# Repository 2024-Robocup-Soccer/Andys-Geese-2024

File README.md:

<h1 align="center" id="title">Robocup Soccer</h1>

<p id="description">A Lightweight Soccer Robot for Robocup Junior. Created by Matteo Cericola, John Qing, Sean Yien and Yuan Yoshimi. </p>

Documentation: https://andys-geese-2024.readthedocs.io/en/latest/

RoboCup is an international robotics tournament held around the world every year. More information can be found here: https://www.robocup.org/. The tournament we participated in this year was RoboCup Junior Lightweight.

<h2>Competition and Awards</h2>

2024 RCJ National Soccer Champion (Toronto)

2024 RCJ Regional Soccer Champion (Montreal)

2024 RCJ Regional Soccer Super Team Champion (Montreal)

<h2>3D Model Link</h2>

[https://a360.co/3x0yv2s](https://a360.co/3x0yv2s)

<h2>Project Pictures:</h2>

<h2>💻 Built with</h2>

Technologies used in the project:

*   Fusion 360
*   VS Code (PlatformIO)
*   Prusa MK4 3D Printer
*   Teensy 4.1
*   OpenMv Camera
*   Adafruit BNO085 Compass
*   TSSP4038
*   GTF 50mm Omniwheels
*   GA25YN370 12V 1000RPM Motors
*   Pololu G2 High-Power Motor Driver 18v25
*   Photodiodes

CC BY-SA 4.0

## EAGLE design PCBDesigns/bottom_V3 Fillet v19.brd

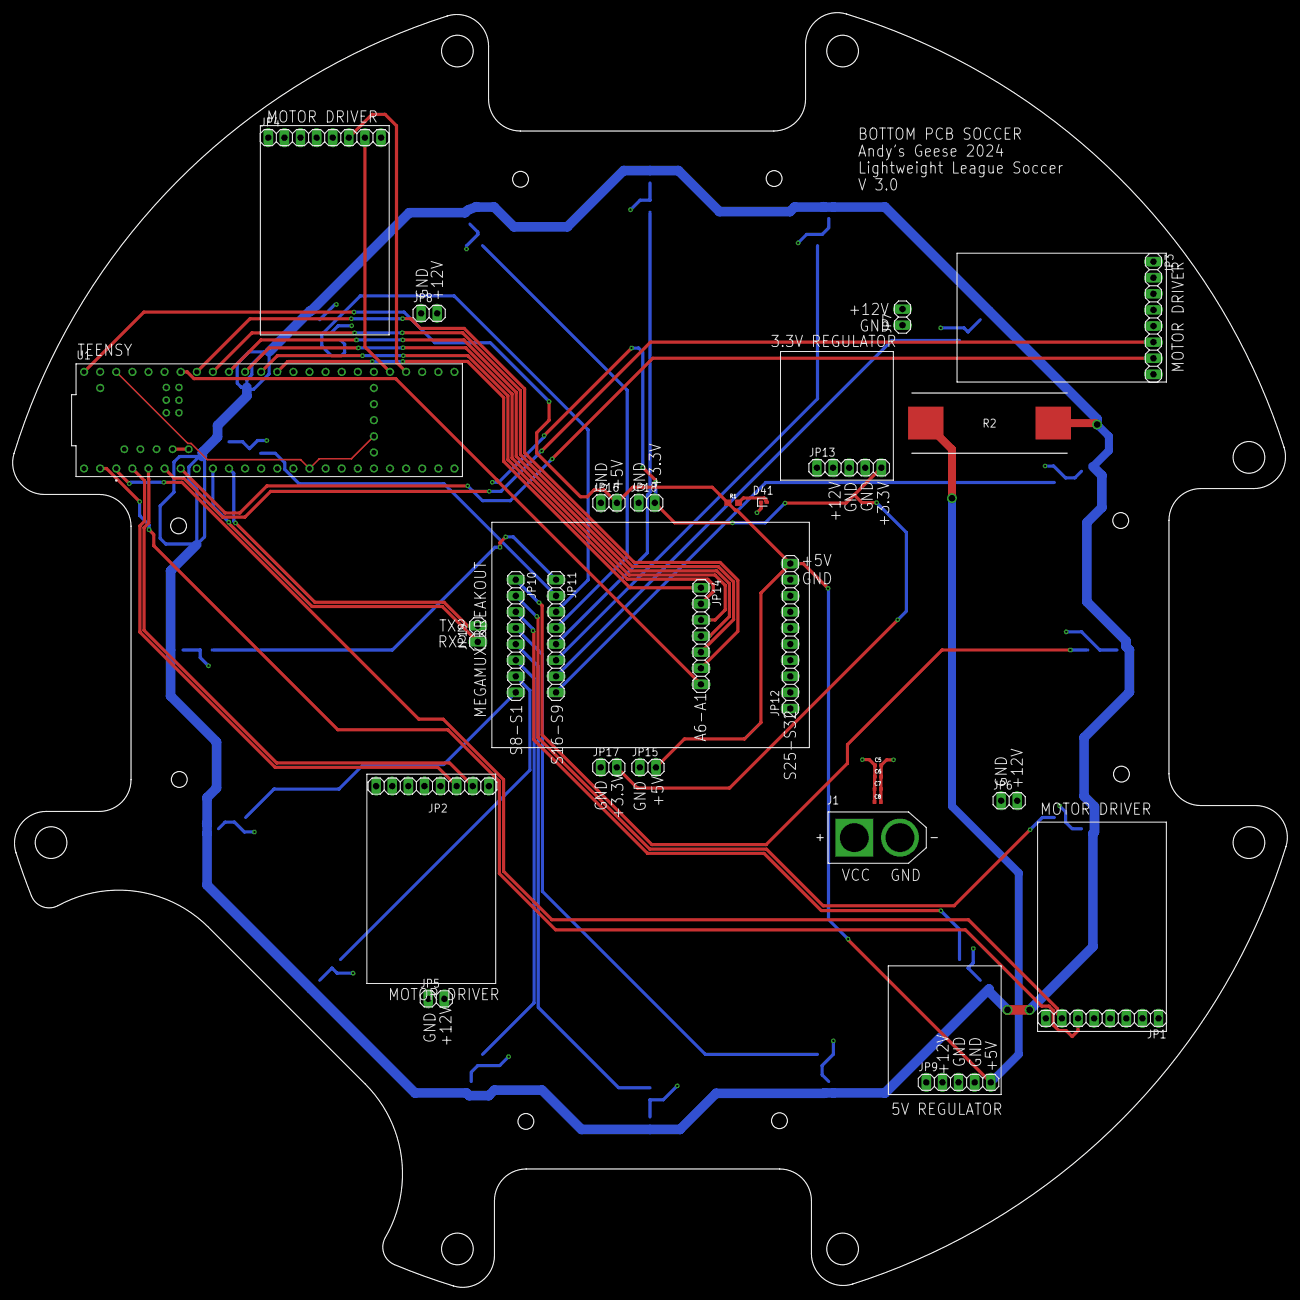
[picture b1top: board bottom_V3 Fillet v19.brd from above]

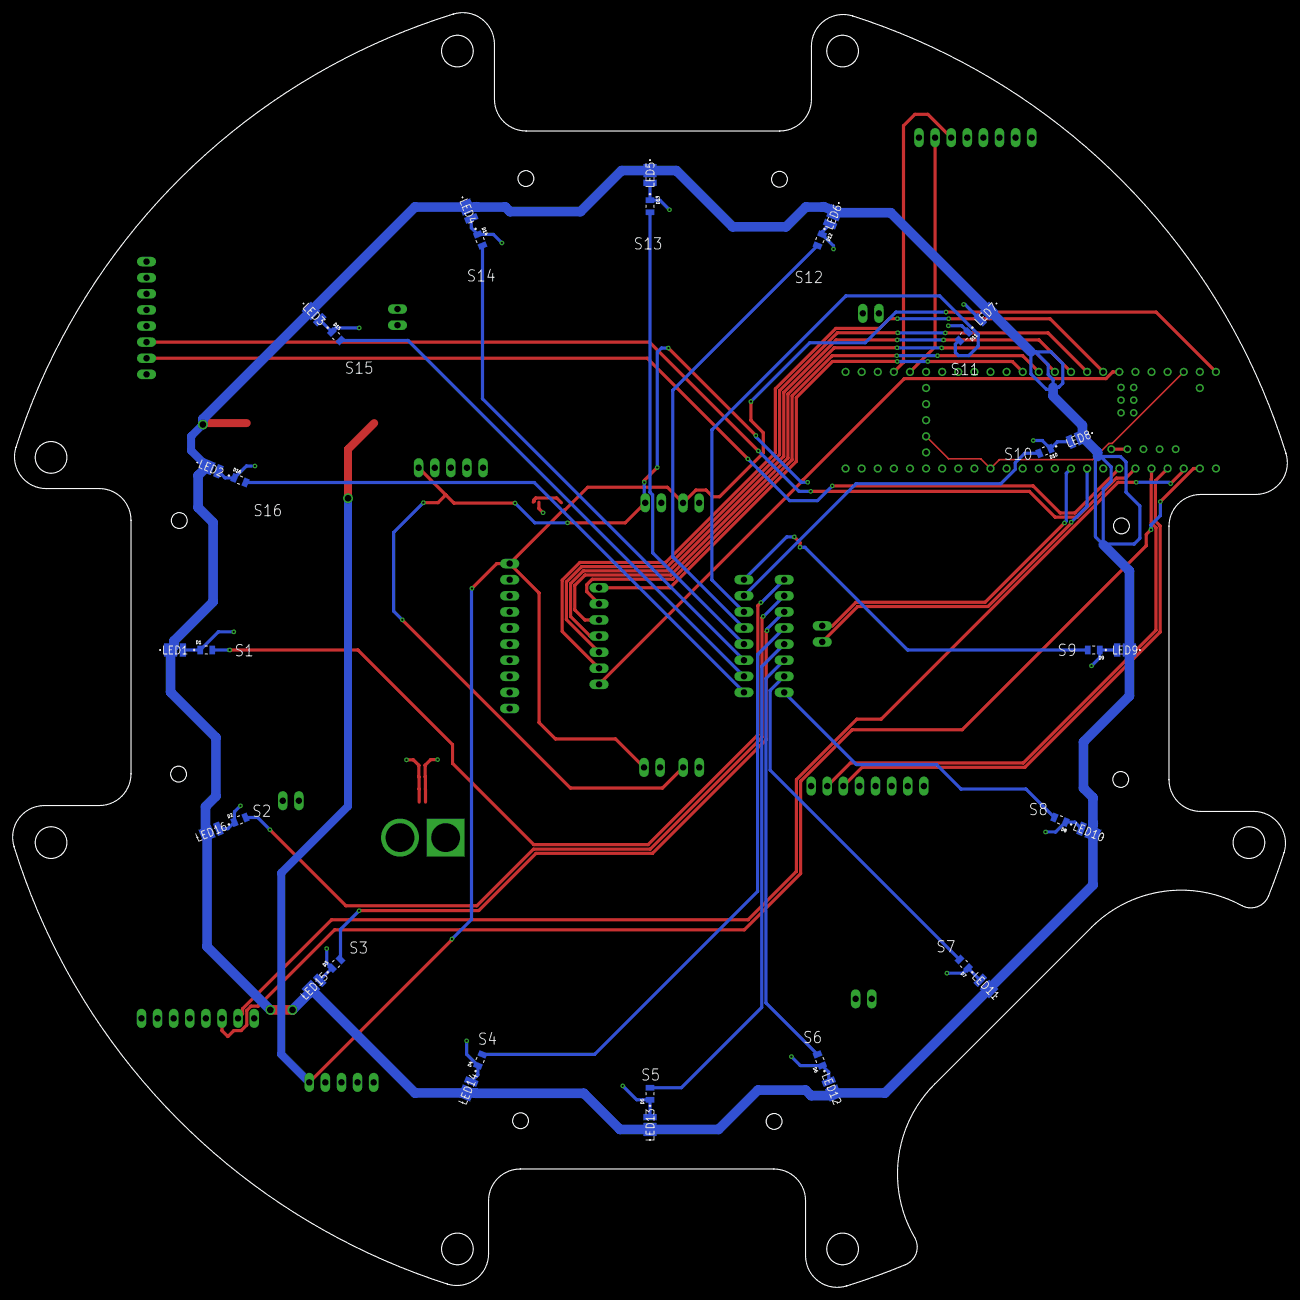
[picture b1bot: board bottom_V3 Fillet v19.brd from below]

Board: 4 copper layers, 201.1 x 201.1 mm, 60 parts (32 on the bottom side), 41 nets.

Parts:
C5, C6, C7, C8: 0.1uF; 0402-TIGHT
D1, D2, D3, D4, D5, D6, D7, D8, D9, D10, D11, D12, D13, D14, D15, D16: 019-141-411-R; DIOC2012X80N
D41: LED_GREEN; LEDC1005X25N_FLAT-G
J1: XT60-M; AMASS_XT60-M
JP1, JP2, JP3, JP4, JP10, JP11: PINHD-1X8; 1X08
JP5, JP6, JP7, JP8, JP15, JP16, JP17, JP18, JP19: PINHD-1X2; 1X02
JP9, JP13: PINHD-1X5; 1X05
JP12: PINHD-1X10; 1X10
JP14: PINHD-1X7; 1X07
LED1, LED2, LED3, LED4, LED5, LED6, LED7, LED8, LED9, LED10, LED11, LED12, LED13, LED14, LED15, LED16: 150283HS73103
R1: 1k; 0603
R2: SMW71R5JT; RESM24595X990N
U1: DEV-16771; MODULE_DEV-16771

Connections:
0: JP1.6, U1.0
1: JP1.7, U1.1
2: JP2.6, U1.2
3: JP2.7, U1.3
3.3V: U1.3.3V_1, U1.3.3V_2, U1.3.3V_3
4: JP3.6, U1.4
5: JP3.7, U1.5
36: JP4.6, U1.36
37: JP4.7, U1.37
+3.3V: JP13.5, JP17.2, JP18.2
+5V: JP9.5, JP12.10, JP15.2, JP16.2, R1.1, R2.1, U1.VIN
A0: JP14.1, U1.14
A1: JP14.2, U1.15
A2: JP14.3, U1.16
A3: JP14.4, U1.17
A4: JP14.5, U1.18
A5: JP14.6, U1.19
A6: JP14.7, U1.20
GND: C5.2, C6.2, C7.2, C8.2, D1.K, D2.K, D3.K, D4.K, D5.K, D6.K, D7.K, D8.K, D9.K, D10.K, D11.K, D12.K, D13.K, D14.K, D15.K, D16.K, D41.C, J1.N, JP1.8, JP2.8, JP3.8, JP4.8, JP5.1, JP6.1, JP7.1, JP8.1, JP9.3, JP9.4, JP12.9, JP13.3, JP13.4, JP15.1, JP16.1, JP17.1, JP18.1, LED1.2, LED2.2, LED3.2, LED4.2, LED5.2, LED6.2, LED7.2, LED8.2, LED9.2, LED10.2, LED11.2, LED12.2, LED13.2, LED14.2, LED15.2, LED16.2, U1.GND1, U1.GND2, U1.GND3, U1.GND4, U1.GND5
unnamed: LED1.1, LED2.1, LED3.1, LED4.1, LED5.1, LED6.1, LED7.1, LED8.1, LED9.1, LED10.1, LED11.1, LED12.1, LED13.1, LED14.1, LED15.1, LED16.1, R2.2
unnamed: D41.A, R1.2
RX2: JP19.1, U1.7
S1: D1.A, JP10.1
S2: D2.A, JP10.2
S3: D3.A, JP10.3
S4: D4.A, JP10.4
S5: D5.A, JP10.5
S6: D6.A, JP10.6
S7: D7.A, JP10.7
S8: D8.A, JP10.8
S9: D9.A, JP11.1
S10: D10.A, JP11.2
S11: D11.A, JP11.3
S12: D12.A, JP11.4
S13: D13.A, JP11.5
S14: D14.A, JP11.6
S15: D15.A, JP11.7
S16: D16.A, JP11.8
TX2: JP19.2, U1.8
USB_GND: U1.USB_GND1, U1.USB_GND2
VCC: C5.1, C6.1, C7.1, C8.1, J1.P, JP5.2, JP6.2, JP7.2, JP8.2, JP9.2, JP13.2

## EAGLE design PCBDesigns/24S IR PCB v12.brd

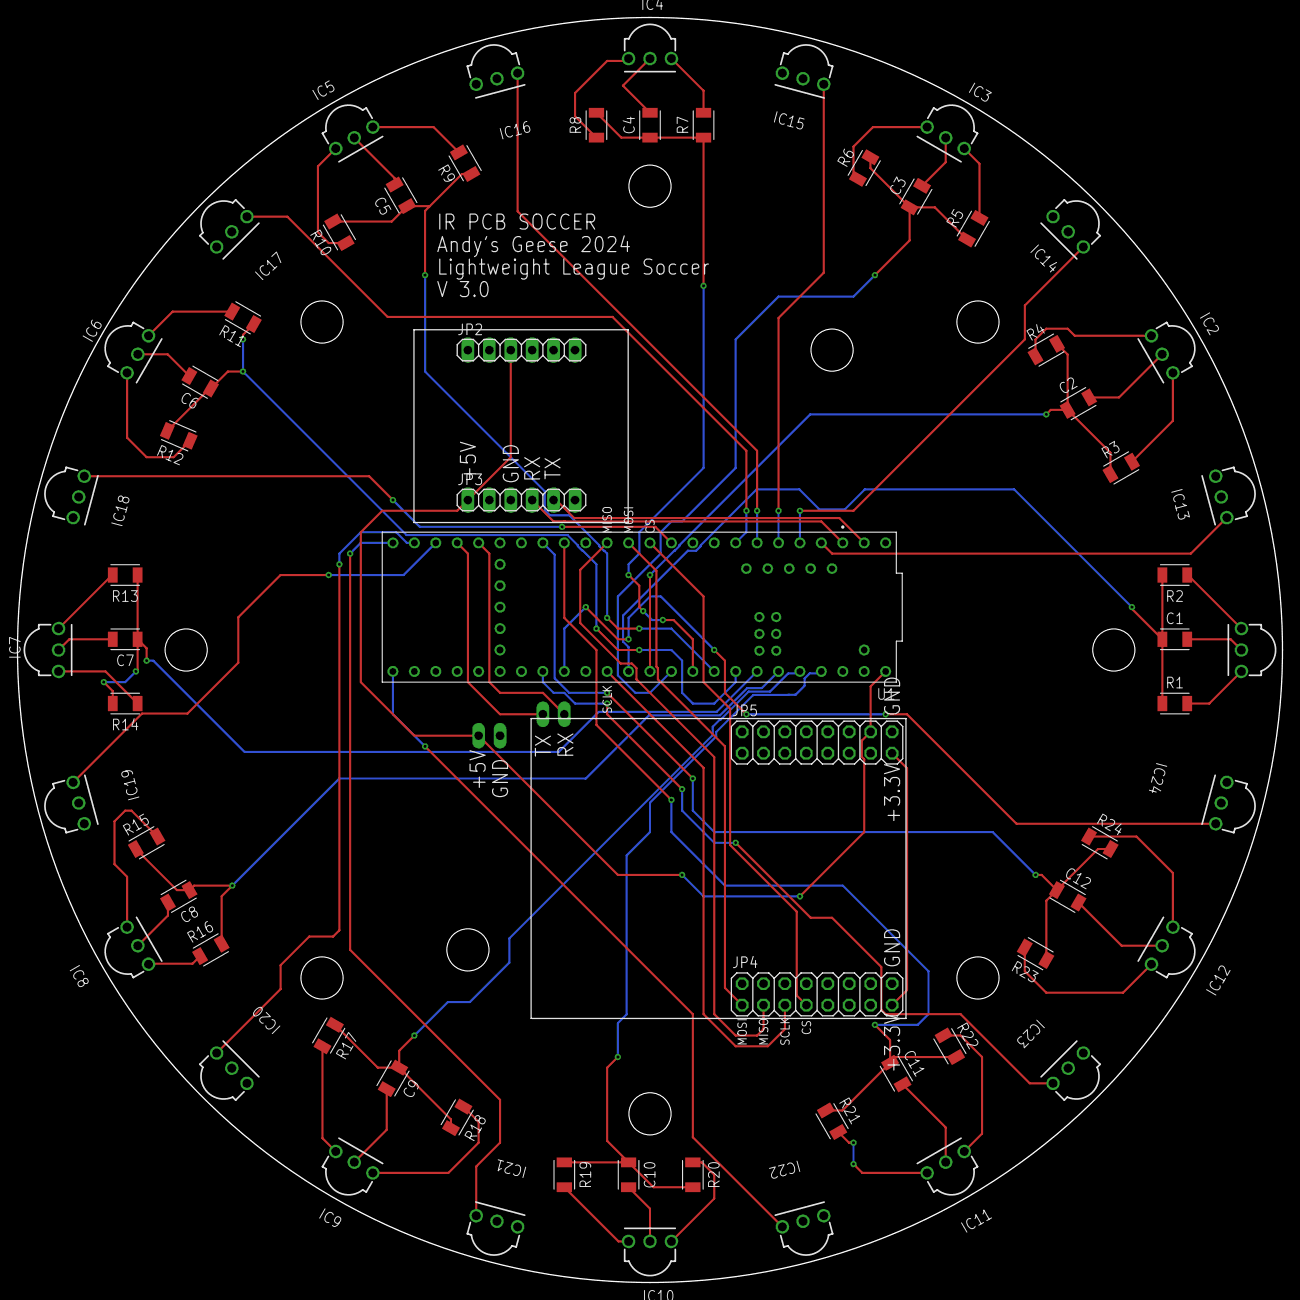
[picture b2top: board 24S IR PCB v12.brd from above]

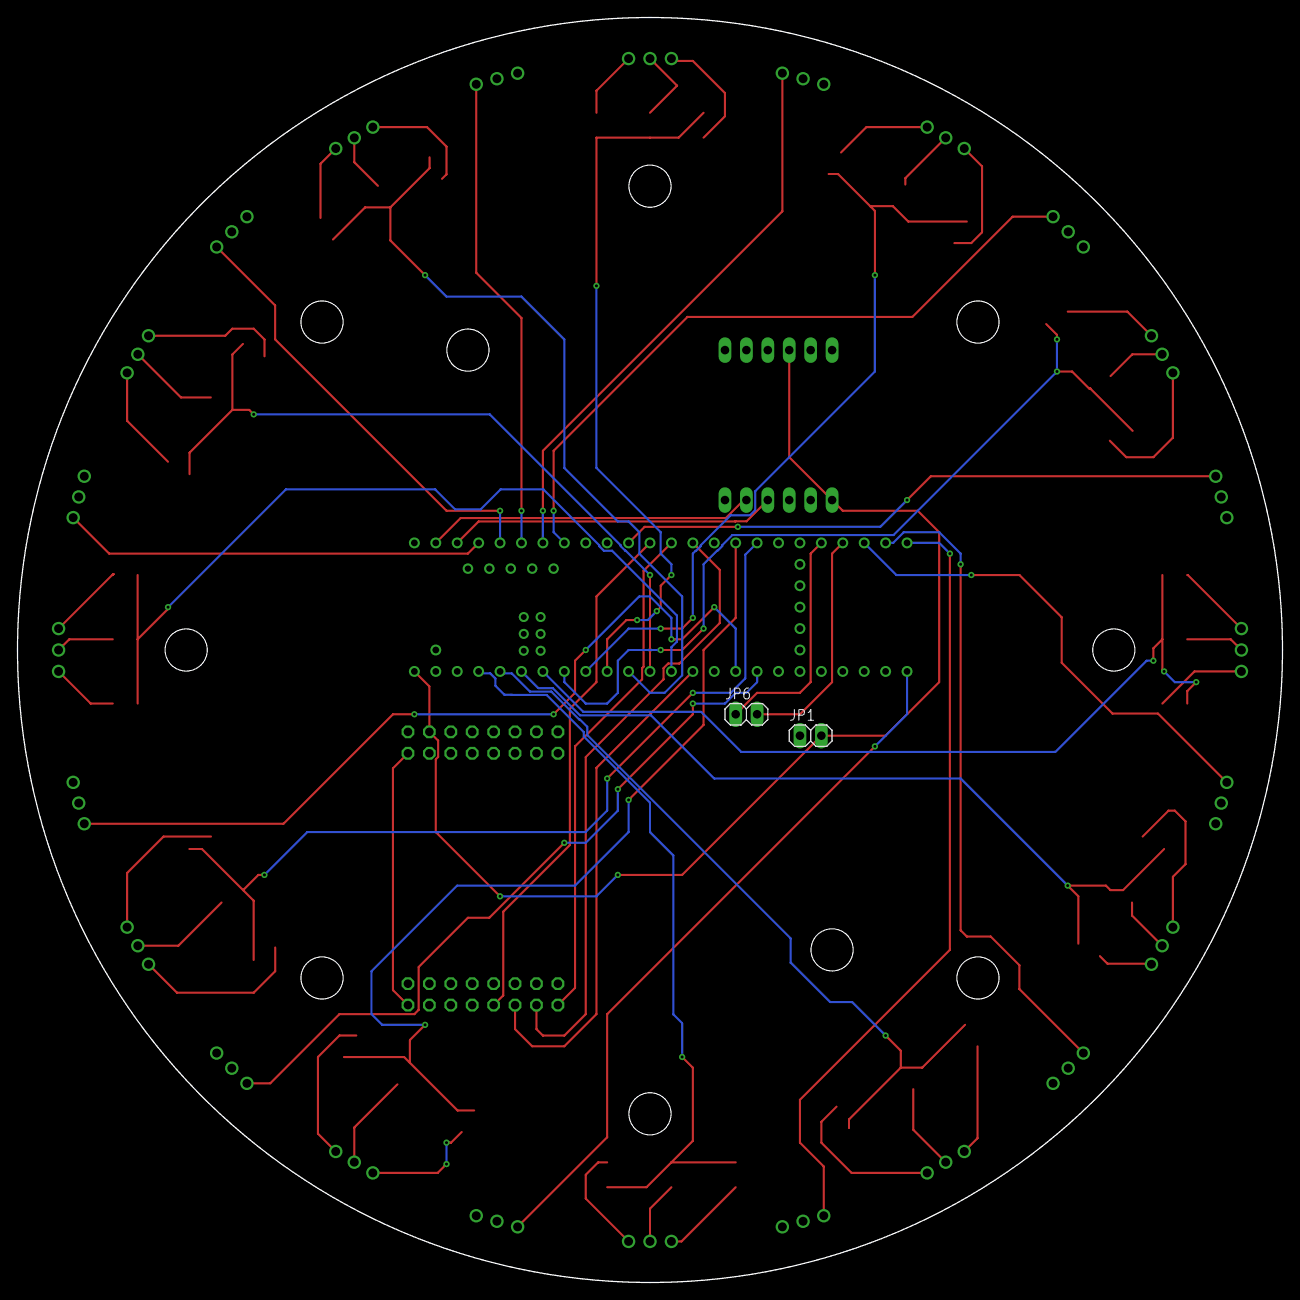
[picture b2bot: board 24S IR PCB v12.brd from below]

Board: 4 copper layers, 150.0 x 150.0 mm, 67 parts (2 on the bottom side), 48 nets.

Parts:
C1, C2, C3, C4, C5, C6, C7, C8, C9, C10, C11, C12: 4.7uF; CAPC3216X135
IC1, IC2, IC3, IC4, IC5, IC6, IC7, IC8, IC9, IC10, IC11, IC12, IC13, IC14, IC15, IC16, IC17, IC18, IC19, IC20, IC21, IC22, IC23, IC24: TSSP4038
JP1, JP6: PINHD-1X2; 1X02
JP2, JP3: PINHD-1X6; 1X06
JP4, JP5: PINHD-2X8; 2X08
R1, R3, R5, R7, R9, R11, R13, R15, R17, R19, R21, R23: 220; RESC3216X70
R2, R4, R6, R8, R10, R12, R14, R16, R18, R20, R22, R24: 10k; RESC3216X70
U1: DEV-16771; MODULE_DEV-16771

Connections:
3.3VRAIL: JP4.15, JP5.15
3V3: IC1.3, IC2.3, IC3.3, IC4.3, IC5.3, IC6.3, IC7.3, IC8.3, IC9.3, IC10.3, IC11.3, IC12.3, IC13.3, IC14.3, IC15.3, IC16.3, IC17.3, IC18.3, IC19.3, IC20.3, IC21.3, IC22.3, IC23.3, IC24.3, R2.1, R4.1, R6.1, R8.1, R10.1, R12.1, R14.1, R16.1, R18.1, R20.1, R22.1, R24.1, U1.3.3V_1, U1.3.3V_2, U1.3.3V_3
+5V: JP1.2, JP2.3, JP3.1, JP5.14, U1.VIN
GND: C1.2, C2.2, C3.2, C4.2, C5.2, C6.2, C7.2, C8.2, C9.2, C10.2, C11.2, C12.2, IC1.2, IC2.2, IC3.2, IC4.2, IC5.2, IC6.2, IC7.2, IC8.2, IC9.2, IC10.2, IC11.2, IC12.2, IC13.2, IC14.2, IC15.2, IC16.2, IC17.2, IC18.2, IC19.2, IC20.2, IC21.2, IC22.2, IC23.2, IC24.2, JP1.1, JP3.3, JP4.16, JP5.16, U1.GND1, U1.GND2, U1.GND3, U1.GND4, U1.GND5, U1.USB_GND1, U1.USB_GND2
unnamed: IC12.1, R23.2
unnamed: IC1.1, R1.2
unnamed: IC2.1, R3.2
unnamed: IC3.1, R5.2
unnamed: IC4.1, R7.2
unnamed: IC5.1, R9.2
unnamed: IC6.1, R11.2
unnamed: IC7.1, R13.2
unnamed: IC8.1, R15.2
unnamed: IC9.1, R17.2
unnamed: IC10.1, R19.2
unnamed: IC11.1, R21.2
P0: JP4.1, U1.11
P1: JP4.3, U1.12
P2: JP4.5, U1.13
P3: JP4.7, U1.10
RX: JP6.1, U1.28
SCL: JP3.4, U1.1
SDA: JP3.5, U1.0
TSSP1: C1.1, R1.1, R2.2, U1.14
TSSP2: C2.1, R3.1, R4.2, U1.15
TSSP3: C3.1, R5.1, R6.2, U1.16
TSSP4: C4.1, R7.1, R8.2, U1.17
TSSP5: C5.1, R9.1, R10.2, U1.18
TSSP6: C6.1, R11.1, R12.2, U1.19
TSSP7: C7.1, R13.1, R14.2, U1.20
TSSP8: C8.1, R15.1, R16.2, U1.21
TSSP9: C9.1, R17.1, R18.2, U1.22
TSSP10: C10.1, R19.1, R20.2, U1.23
TSSP11: C11.1, R21.1, R22.2, U1.24
TSSP12: C12.1, R23.1, R24.2, U1.25
TSSP13: IC13.1, U1.2
TSSP14: IC14.1, U1.3
TSSP15: IC15.1, U1.4
TSSP16: IC16.1, U1.5
TSSP17: IC17.1, U1.6
TSSP18: IC18.1, U1.9
TSSP19: IC19.1, U1.30
TSSP20: IC20.1, U1.31
TSSP21: IC21.1, U1.32
TSSP22: IC22.1, U1.33
TSSP23: IC23.1, U1.40
TSSP24: IC24.1, U1.41
TX: JP6.2, U1.29

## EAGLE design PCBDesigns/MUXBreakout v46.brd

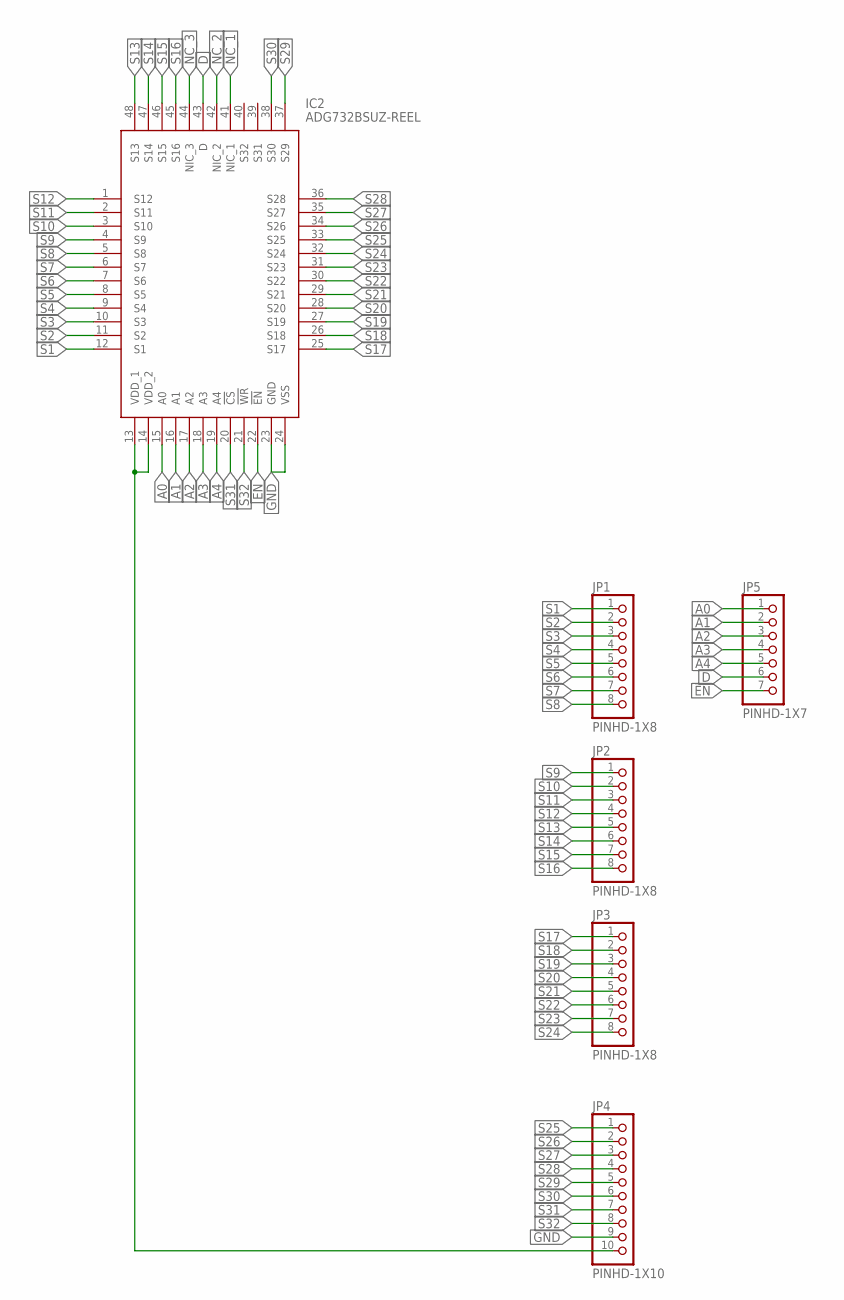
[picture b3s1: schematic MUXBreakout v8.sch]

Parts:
IC2: ADG732BSUZ-REEL; QFP50P900X900X120-48N
JP1, JP2, JP3: PINHD-1X8; 1X08
JP4: PINHD-1X10; 1X10
JP5: PINHD-1X7; 1X07

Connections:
!EN: IC2.22 (!EN), JP5.7
A0: IC2.15 (A0), JP5.1
A1: IC2.16 (A1), JP5.2
A2: IC2.17 (A2), JP5.3
A3: IC2.18 (A3), JP5.4
A4: IC2.19 (A4), JP5.5
D: IC2.43 (D), JP5.6
GND: IC2.23 (GND), IC2.24 (VSS), JP4.9
NC_1: IC2.41 (NIC_1)
NC_2: IC2.42 (NIC_2)
NC_3: IC2.44 (NIC_3)
S1: IC2.12 (S1), JP1.1
S2: IC2.11 (S2), JP1.2
S3: IC2.10 (S3), JP1.3
S4: IC2.9 (S4), JP1.4
S5: IC2.8 (S5), JP1.5
S6: IC2.7 (S6), JP1.6
S7: IC2.6 (S7), JP1.7
S8: IC2.5 (S8), JP1.8
S9: IC2.4 (S9), JP2.1
S10: IC2.3 (S10), JP2.2
S11: IC2.2 (S11), JP2.3
S12: IC2.1 (S12), JP2.4
S13: IC2.48 (S13), JP2.5
S14: IC2.47 (S14), JP2.6
S15: IC2.46 (S15), JP2.7
S16: IC2.45 (S16), JP2.8
S17: IC2.25 (S17), JP3.1
S18: IC2.26 (S18), JP3.2
S19: IC2.27 (S19), JP3.3
S20: IC2.28 (S20), JP3.4
S21: IC2.29 (S21), JP3.5
S22: IC2.30 (S22), JP3.6
S23: IC2.31 (S23), JP3.7
S24: IC2.32 (S24), JP3.8
S25: IC2.33 (S25), JP4.1
S26: IC2.34 (S26), JP4.2
S27: IC2.35 (S27), JP4.3
S28: IC2.36 (S28), JP4.4
S29: IC2.37 (S29), JP4.5
S30: IC2.38 (S30), JP4.6
S31: IC2.20 (!CS), JP4.7
S32: IC2.21 (!WR), JP4.8
VDD_2: IC2.13 (VDD_1), IC2.14 (VDD_2), JP4.10

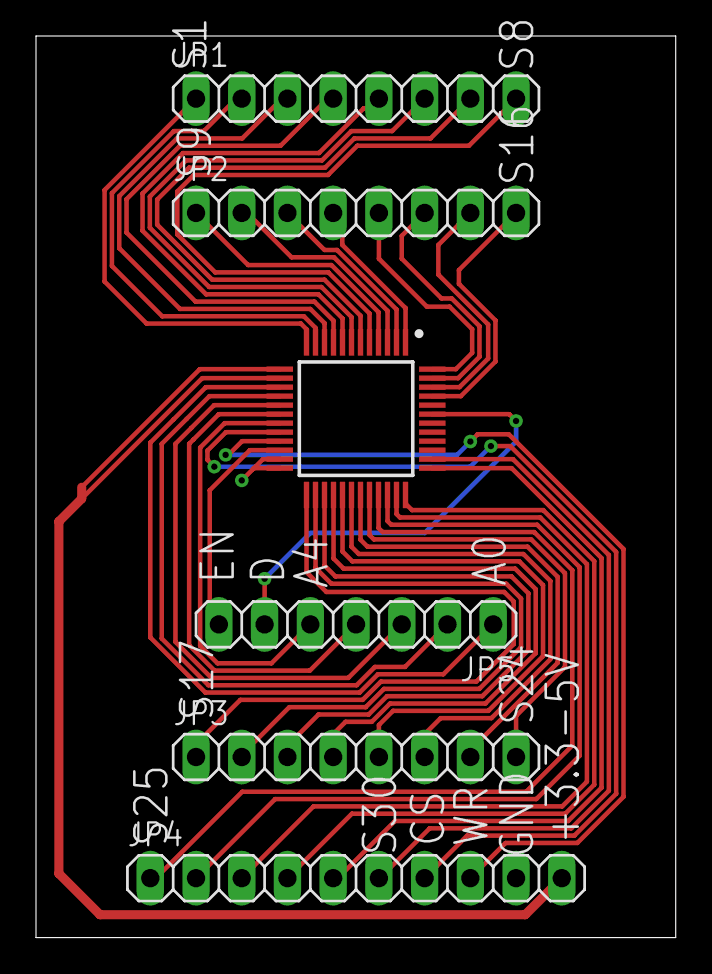
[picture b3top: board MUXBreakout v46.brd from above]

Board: 2 copper layers, 35.5 x 50.1 mm, 6 parts (0 on the bottom side), 41 nets.

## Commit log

2024-06-28 Rename RotationPID.ino to rotationPID.ino
2024-07-01 Photos from shrouded IR sensor calibration
2024-07-01 Rename 2324-RoboCup-SensorData0613-3d-1.png to IR Sensor Hardware/2324-RoboCup-SensorData0613-3d-1.png
2024-07-01 Rename 2324-RoboCup-SensorData0613-3d-1.png to Sensor With Shroud.png
2024-07-01 Rename Sensor With Shroud.png to Sensor 1 With Shroud.png
2024-07-01 Rename 2324-RoboCup-SensorData0613-3d-10.png to IR Sensor Hardware /2324-RoboCup-SensorData0613-3d-10.png
2024-07-01 Rename 2324-RoboCup-SensorData0613-3d-10.png to 2324-RoboCup-SensorData0613-3d-10.png
2024-07-01 Rename 2324-RoboCup-SensorData0613-3d-11.png to IR Sensor Hardware/2324-RoboCup-SensorData0613-3d-11.png
2024-07-01 Rename 2324-RoboCup-SensorData0613-3d-12.png to IR Sensor Hardware/2324-RoboCup-SensorData0613-3d-12.png
2024-07-01 Rename 2324-RoboCup-SensorData0613-3d-3.png to IR Sensor Hardware/2324-RoboCup-SensorData0613-3d-3.png
2024-07-01 Rename 2324-RoboCup-SensorData0613-3d-2.png to IR Sensor Hardware/2324-RoboCup-SensorData0613-3d-2.png
2024-07-01 Rename 2324-RoboCup-SensorData0613-3d-4.png to IR Sensor Hardware/Sensor 4 With Shroud.png
2024-07-01 Rename 2324-RoboCup-SensorData0613-3d-5.png to IR Sensor Hardware/Sensor 5 With Shroud.png
2024-07-01 Rename 2324-RoboCup-SensorData0613-3d-6.png to IR Sensor Hardware/Sensor 6 With Shroud.png
2024-07-01 Rename 2324-RoboCup-SensorData0613-3d-7.png to IR Sensor Hardware/Sensor 7 With Shroud.png
2024-07-01 Rename 2324-RoboCup-SensorData0613-3d-8.png to IR Sensor Hardware/Sensor 8 With Shroud.png
2024-07-01 Rename 2324-RoboCup-SensorData0613-3d-9.png to IR Sensor Hardware/Sensor 9 With Shroud.png
2024-07-01 Rename 2324-RoboCup-SensorData0613-3d-10.png to Sensor 10 With Shroud.png
2024-07-01 Rename 2324-RoboCup-SensorData0613-3d-3.png to Sensor 3 With Shroud.png
2024-07-01 Rename 2324-RoboCup-SensorData0613-3d-2.png to Sensor 2 With Shroud.png
2024-07-01 Rename 2324-RoboCup-SensorData0613-3d-12.png to Sensor 12 With Shroud.png
2024-07-01 Rename 2324-RoboCup-SensorData0613-3d-11.png to Sensor 11 With Shroud.png
2024-07-01 Update Heat Maps.md
    Added full description of data collection methods
2024-07-01 Added the irCalibration.ino file
    This file was used for the data collection to make the plots shown
2024-07-01 Rename SensorCalibration.ino to irCalibration.ino
2024-07-01 Rename IR Sensor Hardware/Heat Maps.md to IR Sensor Hardware/Heat Maps/Heat Maps.md
2024-07-01 Rename IR Sensor Hardware/Sensor 1 With Shroud.png to IR Sensor Hardware/Heat Maps/Sensor 1 With Shroud.png
2024-07-01 Rename IR Sensor Hardware/Sensor 10 With Shroud.png to IR Sensor Hardware/Heat Maps/Sensor 10 With Shroud.png
2024-07-01 Rename IR Sensor Hardware/Sensor 11 With Shroud.png to IR Sensor Hardware/Heat Maps/Sensor 11 With Shroud.png
2024-07-01 Rename IR Sensor Hardware/Sensor 12 With Shroud.png to IR Sensor Hardware/Heat Maps/Sensor 12 With Shroud.png
2024-07-01 Rename IR Sensor Hardware/Sensor 2 With Shroud.png to IR Sensor Hardware/Heat Maps/Sensor 2 With Shroud.png
2024-07-01 Rename IR Sensor Hardware/Sensor 3 With Shroud.png to IR Sensor Hardware/Heat Maps/Sensor 3 With Shroud.png
2024-07-01 Rename IR Sensor Hardware/Sensor 7 With Shroud.png to IR Sensor Hardware/Heat Maps/Sensor 7 With Shroud.png
2024-07-01 Rename IR Sensor Hardware/Sensor 4 With Shroud.png to IR Sensor Hardware/Heat Maps/Sensor 4 With Shroud.png
2024-07-01 Rename IR Sensor Hardware/Sensor 5 With Shroud.png to IR Sensor Hardware/Heat Maps/Sensor 5 With Shroud.png
2024-07-01 Rename IR Sensor Hardware/Sensor 6 With Shroud.png to IR Sensor Hardware/Heat Maps/Sensor 6 With Shroud.png
2024-07-01 Rename IR Sensor Hardware/Sensor 8 With Shroud.png to IR Sensor Hardware/Heat Maps/Sensor 8 With Shroud.png
2024-07-01 Rename IR Sensor Hardware/Sensor 9 With Shroud.png to IR Sensor Hardware/Heat Maps/Sensor 9 With Shroud.png
2024-07-01 Create IR Sensor.md
    Simple description of our robot
2024-07-01 Update bottom.cpp
    Move to dead because not being used anymore
2024-07-01 Rename soccer.png to robot.png
2024-07-09 camera code first upload
2024-07-10 Rename notUsed.md to README.md
2024-07-10 Rename 4-21-24 Soccer Code/rotationPID.ino to 4-21-24 Soccer Code/Bottom Code/rotationPID.ino
2024-07-10 Add current working bottom code
    Stays at initial angle using gyro, uses sine wave to move, and once the ball is at sensor 12 or 0 degrees, it moves forward at full speed
2024-07-10 Rename Bottom V3.cpp to Bottom V3.cpp
2024-07-10 renamed files
2024-07-10 formatting fix
2024-07-10 Rename BNO.ino to Compass.cpp
2024-07-11 increase pwm frequency to 1khz
2024-07-11 Rename IRSensorTesting.ino to IRSensorTesting.cpp
2024-07-11 Rename 2024 Soccer/Calibration Code/IRSensorTesting.cpp to Calibration Code/IRSensorTesting.cpp
2024-07-11 Rename CalibrationCode.md to README.md
2024-07-11 Update Compass.cpp
    Changed getBallAngle() to getBotAngle()
2024-07-11 Update Compass.h
    Changed method signature
2024-07-11 Rename Compass.cpp to Compass.cpp
    Changed file location
2024-07-11 Update and rename Compass.h to Compass.h
    Moved file location
2024-07-12 Update motorControlV3.cpp
    Changed pi to PI
2024-07-12 added sphinx docs
2024-07-12 fix yaml
2024-07-13 Create configure
2024-07-13 added new section to docs
2024-07-13 added color sensors to docs
2024-07-13 rebuilt
    last env was not updating for new files
2024-07-13 Rename Soccer Robot 3D Model v91.png to soccerrobot.png
2024-07-13 Rename Slide1.jpg to Poster
2024-07-14 Rename CameraPID.ino to OldCameraPID.ino
2024-07-14 Rename OldCameraPID.ino to OldCameraPID.ino
2024-07-14 Add files via upload
    Code written at house
2024-07-14 fixed color
2024-07-14 pushing prod code
2024-07-16 Update and rename main.cpp to FullPIDMethods.cpp
    File with all of the methods for PID. Still not done
2024-07-18 Create BACKUPV2
2024-07-18 Update BACKUPV2
2024-07-18 Rename YuanComms.cpp to YuanCommsTop.cpp
2024-07-20 added pcb designs
2024-08-05 Create LICENSE
2024-08-05 Update LICENSE

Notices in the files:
parts and their libraries:
SparkFun-Capacitors: Licensing: Creative Commons ShareAlike 4.0 International - https://creativecommons.org/licenses/by-sa/4.0
